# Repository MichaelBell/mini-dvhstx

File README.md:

# Mini RP2350 board for Digital Video

The RP2350's HSTX peripheral supports TMDS encoding, as needed for HDMI/DVI video.

The idea of this board is to provide a minimal board in a similar form factor to the Pico 2, but with an HDMI connector on it, to allow experimenting with HSTX and digital video.

My [DVI for HSTX](https://github.com/MichaelBell/dvhstx) library should be ideal for use with this board.

## Pinout

The left side is the same as the Pico, the right side is different (but somewhat related).

| Left Side | Right Side |
| --------- | ---------- |
| GPIO 0    | VBUS       |
| GPIO 1    | HDMI 5V    |
| Ground    | Ground     |
| GPIO 2    | Not connected |
| GPIO 3    | +3V3       |
| GPIO 4    | GPIO 29 (ADC) |
| GPIO 5    | GPIO 28 (ADC) |
| Ground    | Ground     |
| GPIO 6    | GPIO 23    |
| GPIO 7    | GPIO 22    |
| GPIO 8    | SWD        |
| GPIO 9    | SWCLK      |
| Ground    | Ground     |
| GPIO 10   |            |
| GPIO 11   |            |
| HDMI HPD  |            |

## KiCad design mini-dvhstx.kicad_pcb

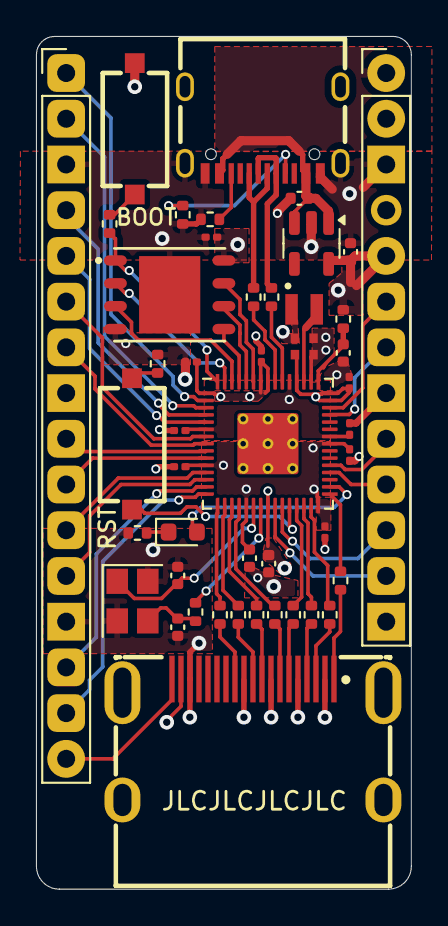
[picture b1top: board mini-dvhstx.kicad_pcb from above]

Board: 4 copper layers, 20.8 x 47.4 mm, 48 parts (1 on the bottom side), 62 nets.

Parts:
BTN1: BOOT; SW-SMD_HX-TS-1101-C-W
BTN2: RST; SW-SMD_HX-TS-1101-C-W
C1, C5: 10uF; C_0402_1005Metric
C2, C8, C11, C12, C13, C14, C15, C16, C17: 100n; C_0201_0603Metric
C3, C4: 13p; C_0402_1005Metric
C6, C7: 4.7u; C_0402_1005Metric_small_pads
C9, C10, C18: 4.7u; C_0402_1005Metric
D1: KT-0603R; LED_0603_1608Metric
J1: USB-C; TYPE-C-SMD_MC-107DJ
J2: HDMI_A; HDMI-SMD_KH-HDMI-19P-CU
J3: Conn_01x16; PinHeader_1x15_P2.54mm_Vertical
J5: Conn_01x13; PinHeader_1x15_P2.54mm_Vertical
L1: 3.3u; L_pol_2016
R1, R2: 5.1k; R_0402_1005Metric
R3, R4, R6, R9: 1k; R_0402_1005Metric
R5: 33; R_0402_1005Metric
R7, R8: 27; R_0402_1005Metric
R12, R13, R14, R15, R16, R17, R18, R19: 270R; R_0402_1005Metric
TP1: TestPoint; TestPoint_Pad_2.0x2.0mm
U1: RP2350_60QFN; RP2350-QFN-60-1EP_7x7_P0.4mm_EP3.4x3.4mm_ThermalVias
U2: AP2112K-3.3; SOT-23-5
U3: W25Q32JV; WSON-8_L6.0-W5.0-P1.27-BL-EP
Y1: ABM8-272-T3; Crystal_SMD_3225-4Pin_3.2x2.5mm

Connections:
+1V1: C7.1, C8.1, C10.1, C11.1, L1.1, TP1.1, U1.6 (DVDD), U1.23 (DVDD), U1.39 (DVDD), U1.50 (VREG_FB)
+3V3: C2.1, C5.1, C6.1, C12.1, C13.1, C14.1, C15.1, C16.1, C17.1, C18.1, J5.5, R5.1, U1.1 (IOVDD), U1.11 (IOVDD), U1.20 (IOVDD), U1.30 (IOVDD), U1.38 (IOVDD), U1.44 (ADC_AVDD), U1.45 (IOVDD), U1.49 (VREG_VIN), U1.53 (USB_OTP_VDD), U1.54 (QSPI_IOVDD), U2.5 (VOUT), U3.8 (VCC)
+5V: C1.1, J1.A4 (VBUS), J1.A9 (VBUS), J5.1, U2.1 (VIN), U2.3 (EN)
/GPIO0: J3.1, U1.2 (GPIO0)
/GPIO1: J3.2, U1.3 (GPIO1)
/GPIO2: J3.4, U1.4 (GPIO2)
/GPIO3: J3.5, U1.5 (GPIO3)
/GPIO4: J3.6, U1.7 (GPIO4)
/GPIO5: J3.7, U1.8 (GPIO5)
/GPIO6: J3.9, U1.9 (GPIO6)
/GPIO7: J3.10, U1.10 (GPIO7)
/GPIO8: J3.11, U1.12 (GPIO8)
/GPIO9: J3.12, U1.13 (GPIO9)
/GPIO10: J3.14, U1.14 (GPIO10)
/GPIO11: J3.15, U1.15 (GPIO11)
/GPIO12: R12.1, U1.16 (GPIO12)
/GPIO13: R13.1, U1.17 (GPIO13)
/GPIO14: R14.1, U1.18 (GPIO14)
/GPIO15: R15.1, U1.19 (GPIO15)
/GPIO16: R16.1, U1.27 (GPIO16)
/GPIO17: R17.1, U1.28 (GPIO17)
/GPIO18: R18.1, U1.29 (GPIO18)
/GPIO19: R19.1, U1.31 (GPIO19)
/GPIO22: J5.10, U1.34 (GPIO22)
/GPIO23: J5.9, U1.35 (GPIO23)
/GPIO28_ADC2: J5.7, U1.42 (GPIO28_ADC2)
/GPIO29_ADC3: J5.6, U1.43 (GPIO29_ADC3)
/HDMI_5V: J2.18 (+5V), J5.2
/HDMI_HPD: J2.19 (HPD), J3.16
/QSPI_SCLK: U1.56 (QSPI_SCLK), U3.6 (CLK)
/QSPI_SD0: U1.57 (QSPI_SD0), U3.5 (DI(IO0))
/QSPI_SD1: U1.59 (QSPI_SD1), U3.2 (DO(IO1))
/QSPI_SD2: U1.58 (QSPI_SD2), U3.3 (IO2)
/QSPI_SD3: U1.55 (QSPI_SD3), U3.7 (IO3)
/QSPI_SS: R6.1, U1.60 (QSPI_SS), U3.1 (~CS)
/RUN: BTN2.2, U1.26 (RUN)
/SWCLK: J5.12, U1.24 (SWCLK)
/SWD: J5.11, U1.25 (SWD)
/VREG_AVDD: C9.1, R5.2, U1.46 (VREG_AVDD)
/VREG_LX: L1.2, U1.48 (VREG_LX)
/XIN: C3.1, U1.21 (XIN), Y1.1
/XOUT: R3.1, U1.22 (XOUT)
/~USB_BOOT: BTN1.2, R6.2
DM: J1.A7 (DN1), J1.B7 (DN2), R8.1
DP: J1.A6 (DP1), J1.B6 (DP2), R7.1
GND: BTN1.1, C1.2, C2.2, C3.2, C4.2, C5.2, C6.2, C7.2, C8.2, C9.2, C10.2, C11.2, C12.2, C13.2, C14.2, C15.2, C16.2, C17.2, C18.2, J1.1 (SHIELD), J1.A1 (GND), J1.A12 (GND), J2.2 (D2S), J2.5 (D1S), J2.8 (D0S), J2.11 (CKS), J2.17 (GND), J2.20 (SH), J2.21 (SH), J2.22 (SH), J2.23 (SH), J3.3, J3.8, J3.13, J5.3, J5.8, J5.13, R1.2, R2.2, R4.2, R9.2, U1.47 (VREG_PGND), U1.61 (GND), U2.2 (GND), U3.4 (GND), U3.9 (EP), Y1.2, Y1.4
GPIO20: D1.2 (A), U1.32 (GPIO20)
unnamed: BTN2.1, R4.1
unnamed: C4.1, R3.2, Y1.3
unnamed: D1.1 (K), R9.1
unnamed: J1.A5 (CC1), R1.1
unnamed: J1.B5 (CC2), R2.1
unnamed: J2.10 (CK+), R13.2
unnamed: J2.12 (CK-), R12.2
unnamed: J2.7 (D0+), R15.2
unnamed: J2.9 (D0-), R14.2
unnamed: J2.4 (D1+), R17.2
unnamed: J2.6 (D1-), R16.2
unnamed: J2.1 (D2+), R19.2
unnamed: J2.3 (D2-), R18.2
unnamed: R8.2, U1.51 (USB_DM)
unnamed: R7.2, U1.52 (USB_DP)

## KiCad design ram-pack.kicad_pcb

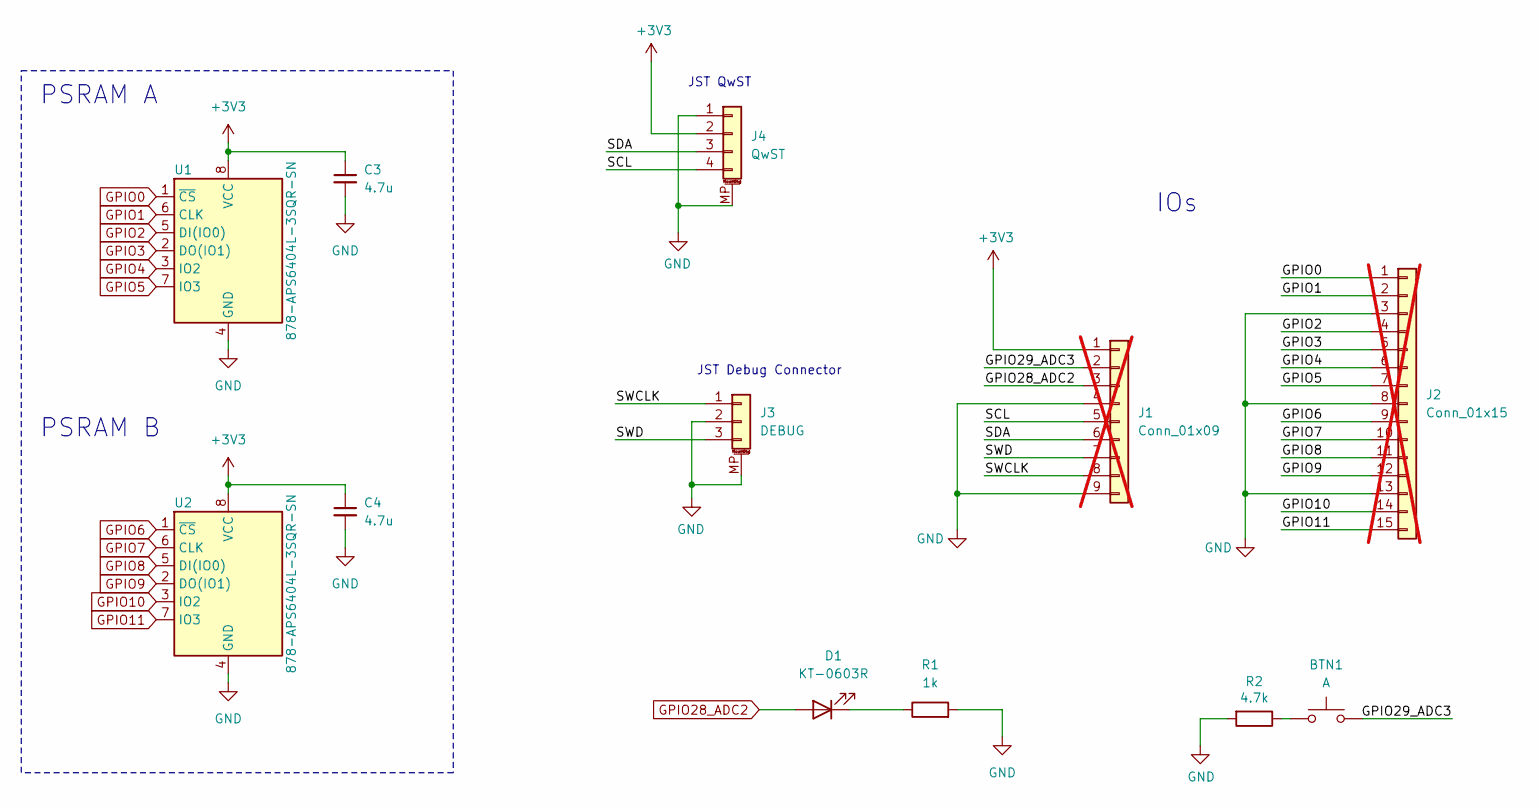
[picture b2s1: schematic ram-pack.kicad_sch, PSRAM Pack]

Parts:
BTN1: A; SW-SMD_HX-TS-1101-C-W; JLC C36498960
C3, C4: 4.7u; C_0402_1005Metric; MPN C0402C105M9PAC
D1: KT-0603R; LED_0603_1608Metric; JLC C2286
J1: Conn_01x09; PinSocket_1x09_P2.54mm_Vertical; not fitted
J2: Conn_01x15; PinSocket_1x15_P2.54mm_Vertical; not fitted
J3: DEBUG; JST_SH_SM03B-SRSS-TB_1x03-1MP_P1.00mm_Horizontal; JLC C160403
J4: QwST; JST_SH_BM04B-SRSS-TB_1x04-1MP_P1.00mm_Vertical; JLC C160390
R1: 1k; R_0402_1005Metric
R2: 4.7k; R_0402_1005Metric
U1, U2: 878-APS6404L-3SQR-SN; SOP-8_3.9x4.9mm_P1.27mm; MPN APS6404L-3SQR-SN; JLC C5333729

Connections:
+3V3: C3.1, C4.1, J1.1, J4.2, U1.8 (VCC), U2.8 (VCC)
/GPIO29_ADC3: BTN1.2, J1.2
/SCL: J1.5, J4.4
/SDA: J1.6, J4.3
/SWCLK: J1.8, J3.1
/SWD: J1.7, J3.3
GND: C3.2, C4.2, J1.4, J1.9, J2.3, J2.8, J2.13, J3.2, J3.MP (MountPin), J4.1, J4.MP (MountPin), R1.2, R2.2, U1.4 (GND), U2.4 (GND)
GPIO0: J2.1, U1.1 (~CS)
GPIO1: J2.2, U1.6 (CLK)
GPIO2: J2.4, U1.5 (DI(IO0))
GPIO3: J2.5, U1.2 (DO(IO1))
GPIO4: J2.6, U1.3 (IO2)
GPIO5: J2.7, U1.7 (IO3)
GPIO6: J2.9, U2.1 (~CS)
GPIO7: J2.10, U2.6 (CLK)
GPIO8: J2.11, U2.5 (DI(IO0))
GPIO9: J2.12, U2.2 (DO(IO1))
GPIO10: J2.14, U2.3 (IO2)
GPIO11: J2.15, U2.7 (IO3)
GPIO28_ADC2: D1.2 (A), J1.3
unnamed: BTN1.1, R2.1
unnamed: D1.1 (K), R1.1

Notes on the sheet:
IOs
JST QwST
JST Debug Connector
PSRAM B
PSRAM A

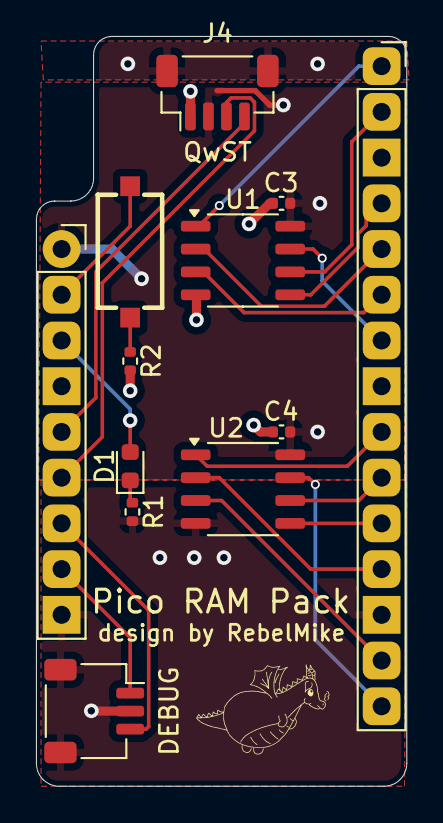
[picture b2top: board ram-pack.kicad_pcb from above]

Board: 4 copper layers, 20.6 x 41.7 mm, 12 parts (0 on the bottom side), 22 nets.

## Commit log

2025-02-15 Redesign
2025-02-15 Complete routing
2025-02-15 Add pinout
2025-02-15 Add schematic
2025-02-15 LICENSE
2025-02-15 Silkscreen
2025-02-16 RAM pack
2025-02-17 Tweaks
2025-03-08 Moving towards v1
2025-03-09 First version
2025-03-21 PSRAM test from Pico2/Mini DVHSTX
